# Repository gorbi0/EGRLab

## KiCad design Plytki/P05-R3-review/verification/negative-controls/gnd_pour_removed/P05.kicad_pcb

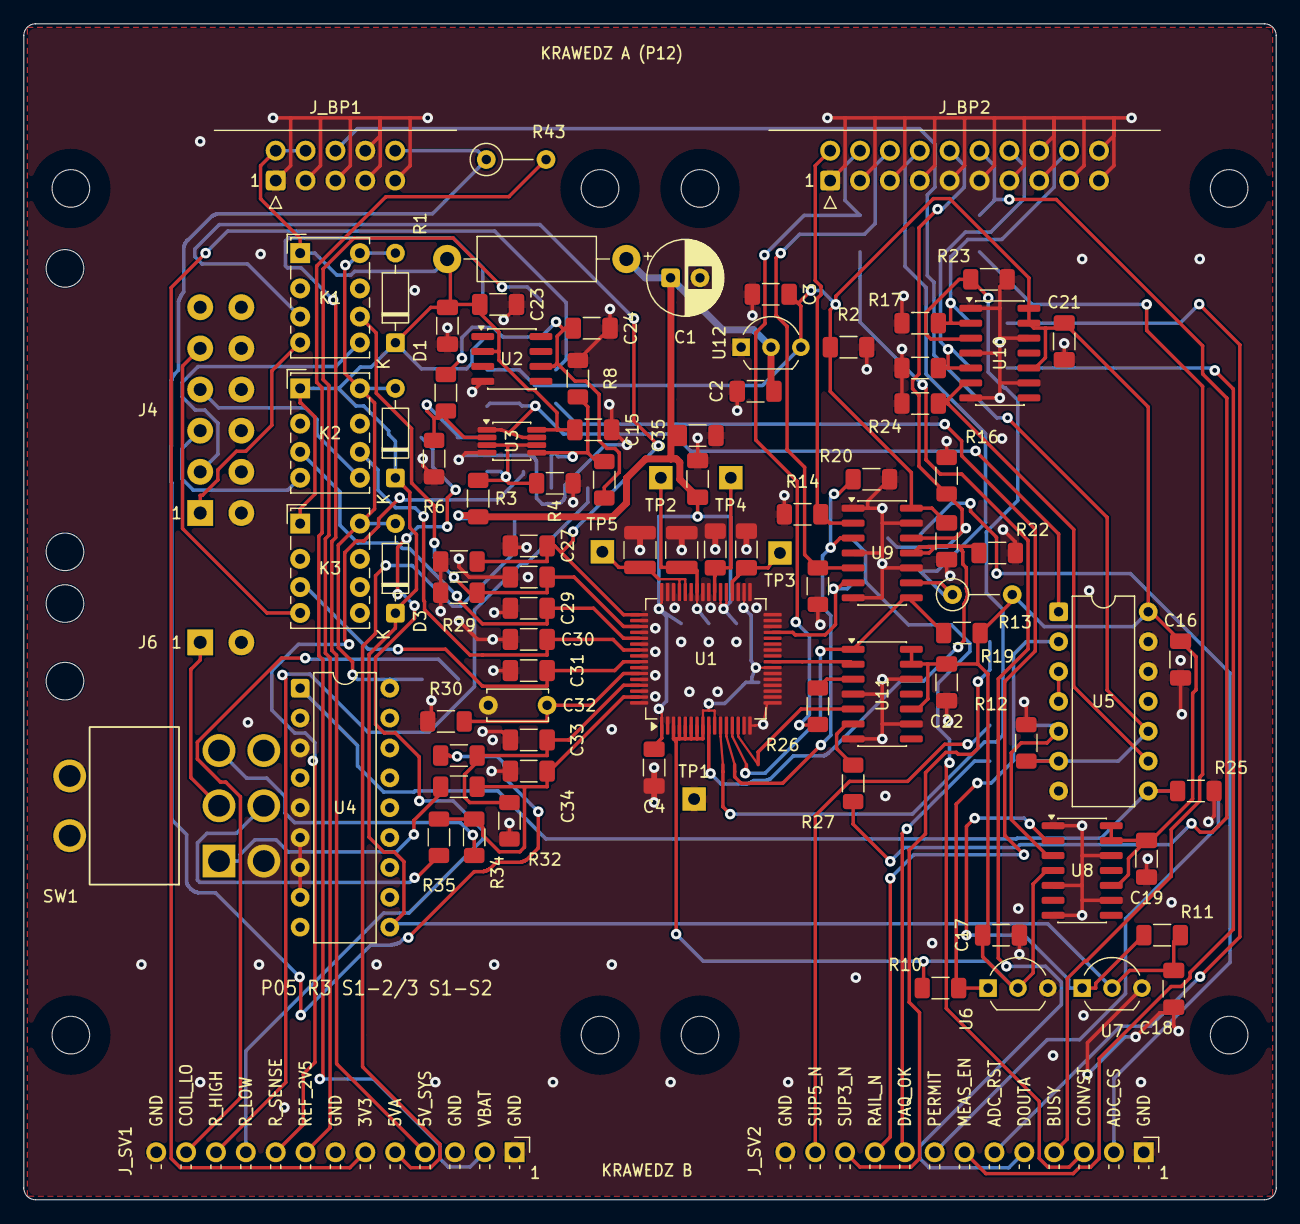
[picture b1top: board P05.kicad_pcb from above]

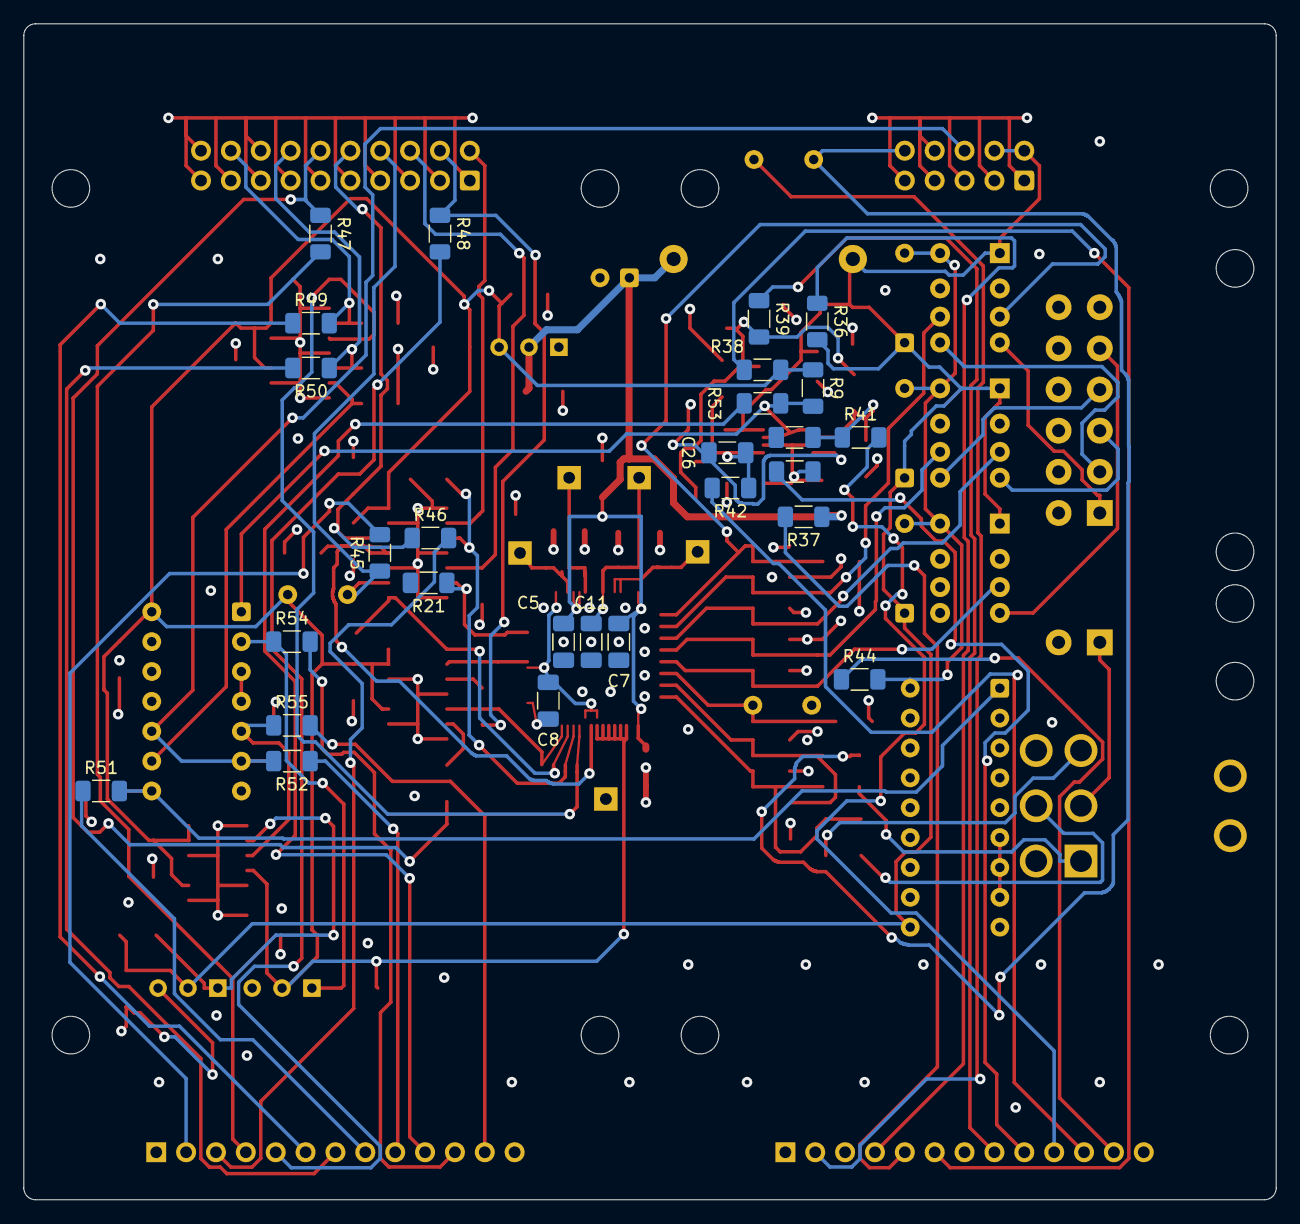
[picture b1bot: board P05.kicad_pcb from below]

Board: 2 copper layers, 106.5 x 100.0 mm, 128 parts (27 on the bottom side), 76 nets.

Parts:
C1: 220u / 16V; CP_Radial_D6.3mm_P2.50mm
C2, C9, C10, C23, C24: 1u; C_1206_3216Metric_Pad1.33x1.80mm_HandSolder
C3: 2.2u; C_1206_3216Metric_Pad1.33x1.80mm_HandSolder
C4, C5, C6, C7, C8, C11, C14, C15, C16, C17, C18, C19, C20, C21, C22: 100n; C_1206_3216Metric_Pad1.33x1.80mm_HandSolder
C12, C13: 22u; C_1210_3225Metric
C25, C26: 10n; C_1206_3216Metric_Pad1.33x1.80mm_HandSolder
C27, C28, C29, C30, C31, C33, C34: 220p; C_1206_3216Metric_Pad1.33x1.80mm_HandSolder
C32: 1n; C_Disc_D5.0mm_W2.5mm_P5.00mm
C35: 10u; C_1206_3216Metric_Pad1.33x1.80mm_HandSolder
D1, D2, D3: 1N4148; D_DO-35_SOD27_P7.62mm_Horizontal
H1, H2, H3, H4, H5, H6, H7, H8: M3 NPTH
J4: TAPS / PTH; PTH_TAPS_12
J6: AUX / coax 50mm; PTH_AUX_2
J_BP1: J_BP1 / IDC 2x5; IDC-Header_2x05_P2.54mm_Horizontal
J_BP2: J_BP2 / IDC 2x10; IDC-Header_2x10_P2.54mm_Horizontal
J_SV1: J_SV1 SERWIS 1x13; PinHeader_1x13_P2.54mm_Horizontal
J_SV2: J_SV2 SERWIS 1x13; PinHeader_1x13_P2.54mm_Horizontal
K1, K2, K3: G6K-2P-Y DC5; Relay_DPDT_Omron_G6K-2P-Y
R1: 1R; R_Axial_DIN0411_L9.9mm_D3.6mm_P15.24mm_Horizontal
R2, R36, R37, R38, R44, R45, R46, R47, R48, R49, R50, R51, R52, R55: 1K; R_1206_3216Metric_Pad1.30x1.75mm_HandSolder
R3: 15K; R_1206_3216Metric_Pad1.30x1.75mm_HandSolder
R4, R9, R10, R11, R12, R14, R15, R16, R17, R18, R19, R20, R21, R22, R23, R24, R25, R30, R39, R40, R41, R42, R53, R54: 10K; R_1206_3216Metric_Pad1.30x1.75mm_HandSolder
R5: 6.04K; R_1206_3216Metric_Pad1.30x1.75mm_HandSolder
R6: 20K; R_1206_3216Metric_Pad1.30x1.75mm_HandSolder
R7: 5.11K; R_1206_3216Metric_Pad1.30x1.75mm_HandSolder
R8: 24.9K; R_1206_3216Metric_Pad1.30x1.75mm_HandSolder
R13: 47K; R_Axial_DIN0207_L6.3mm_D2.5mm_P5.08mm_Vertical
R26, R27: 33R; R_1206_3216Metric_Pad1.30x1.75mm_HandSolder
R28, R29, R32, R34, R35: 100K; R_1206_3216Metric_Pad1.30x1.75mm_HandSolder
R31: 499K; R_1206_3216Metric_Pad1.30x1.75mm_HandSolder
R33: 300K; R_1206_3216Metric_Pad1.30x1.75mm_HandSolder
R43: 4.7K; R_Axial_DIN0207_L6.3mm_D2.5mm_P5.08mm_Vertical
SW1: AUX HI / LO; ESW_100DP_M6
TP1: GND; TestPad_1
TP2: ADC_REF; TestPad_1
TP3: REGCAP_A; TestPad_1
TP4: REGCAP_D; TestPad_1
TP5: REFCAP; TestPad_1
U1: AD7606BBSTZ; LQFP-64_10x10mm_P0.5mm
U2: REF5025IDR; SOIC-8_3.9x4.9mm_P1.27mm
U3: TLV1702-Q1; VSSOP-8_3x3mm_P0.65mm
U4: TBD62083APG; DIP-18_W7.62mm
U5: SN74HC08N; DIP-14_W7.62mm
U6: MCP120-300DI/TO; TO-92_Inline_Wide
U7: MCP120-450DI/TO; TO-92_Inline_Wide
U8, U9, U10, U11: 74LVC125AD; SOIC-14_3.9x8.7mm_P1.27mm
U12: MCP1700-3302E/TO; TO-92_Inline_Wide

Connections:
3V3_DAQ: C3.1, C8.1, C16.1, C17.1, C19.1, C20.1, C21.1, C22.1, R2.1, R9.2, R10.2, R13.2, R19.2, R38.1, U1.3, U1.4, U1.5, U1.6, U1.7, U1.8, U1.10, U1.23, U1.34, U5.14, U6.2, U8.4, U8.10, U8.13, U8.14, U9.14, U10.10, U10.13, U10.14, U11.10, U11.13, U11.14, U12.3
5VA_P05: C1.1, C2.1, C4.1, C5.1, C6.1, C7.1, C35.1, R1.2, R3.1, R37.1, U1.1, U1.37, U1.38, U1.48, U12.2
5V_SYS: C14.1, C15.1, C18.1, C23.1, D1.1, D2.1, D3.1, J_BP1.2, J_BP1.4, K1.1, K2.1, K3.1, R1.1, R11.2, R36.1, U2.2, U3.8, U4.10, U7.2
/AUX_IN/AUX_HI: R33.1, SW1.1
/AUX_IN/AUX_IN: J6.1, SW1.2
/AUX_IN/AUX_LO: R34.1, SW1.3
/AUX_IN/AUX_SHUNT: R35.2, SW1.5
/DIG/BUSY_SER: R27.1, U11.6
/DIG/DOUT_SER: R26.1, U11.3
/READY/DAQ_TWO_OK: U5.3, U5.4
/READY/P05_SUP5_RAW: R11.1, U7.1, U8.2
/SERWIS/SRV_3V3_DAQ: J_SV1.6, R38.2
/SERWIS/SRV_5VA_P05: J_SV1.5, R37.2
/SERWIS/SRV_5V_SYS: J_SV1.4, R36.2
/SERWIS/SRV_ADC_BUSY: J_SV2.4, R47.2
/SERWIS/SRV_ADC_CONVST: J_SV2.3, R46.2
/SERWIS/SRV_ADC_CS: J_SV2.2, R45.2
/SERWIS/SRV_ADC_DOUTA: J_SV2.5, R48.2
/SERWIS/SRV_ADC_RESET: J_SV2.6, R49.2
/SERWIS/SRV_DAQ_OK: J_SV2.9, R52.2
/SERWIS/SRV_DAQ_RAIL_N: J_SV2.10, R53.2
/SERWIS/SRV_MEAS_COIL_LOW: J_SV1.12, R44.2
/SERWIS/SRV_MEAS_EN: J_SV2.7, R50.2
/SERWIS/SRV_MEAS_PERMIT: J_SV2.8, R51.2
/SERWIS/SRV_P05_SUP3_N: J_SV2.11, R54.2
/SERWIS/SRV_P05_SUP5_N: J_SV2.12, R55.2
/SERWIS/SRV_RAIL_HIGH: J_SV1.11, R42.2
/SERWIS/SRV_RAIL_LOW: J_SV1.10, R41.2
/SERWIS/SRV_RAIL_SENSE: J_SV1.9, R40.2
/SERWIS/SRV_REF_2V5: J_SV1.8, R39.2
/SERWIS/SRV_VBAT_SENSE: J_SV1.2, R43.2
ADC_BUSY: J_BP2.12, R27.2, R47.1
ADC_CH1: C27.1, K1.3, R28.1, U1.49
ADC_CH2: C28.1, K1.6, R29.1, U1.51
ADC_CH3: C29.1, K2.3, U1.53
ADC_CH4: C30.1, K2.6, U1.55
ADC_CH5: C31.1, K3.3, U1.57
ADC_CH6: C32.1, R30.1, U1.59
ADC_CH7: C33.1, R31.2, R32.1, U1.61
ADC_CH8: C34.1, R33.2, R34.2, R35.1, U1.63
ADC_CONVST: J_BP2.10, R16.1, R46.1, U9.12
ADC_CONVST_P05: R22.1, U1.9, U9.11
ADC_CS: J_BP2.8, R13.1, R45.1, U9.9
ADC_CS_P05: R19.1, U1.13, U9.8, U11.1
ADC_DOUTA: J_BP2.4, R26.2, R48.1
ADC_REF: C11.1, C12.1, TP2.1, U1.42
ADC_RESET: J_BP2.18, R17.1, R49.1, U10.2
ADC_RESET_P05: R23.1, U1.11, U10.3
ADC_SCLK: J_BP2.2, R14.1, U9.2
ADC_SCLK_P05: R20.1, U1.12, U9.3
ADC_SDI: J_BP2.6, R15.1, U9.5
ADC_SDI_P05: R21.1, U1.29, U9.6
AD_BUSY_LOCAL: U1.14, U11.5
AD_DOUT_LOCAL: U1.24, U11.2
DAQ_OK: J_BP1.6, R12.1, R52.1, U5.6, U5.10
DAQ_RAIL_N: R9.1, R53.1, U3.1, U3.7, U5.1
GND: C1.2, C2.2, C3.2, C4.2, C5.2, C6.2, C7.2, C8.2, C9.2, C10.2, C11.2, C12.2, C13.2, C14.2, C15.2, C16.2, C17.2, C18.2, C19.2, C20.2, C21.2, C22.2, C23.2, C24.2, C25.2, C26.2, C27.2, C28.2, C29.2, C30.2, C31.2, C32.2, C33.2, C34.2, C35.2, J4.2, J4.4, J4.6, J4.8, J4.10, J6.2, J_BP1.1, J_BP1.3, J_BP1.5, J_BP1.7, J_BP1.8, J_BP1.9, J_BP2.1, J_BP2.3, J_BP2.5, J_BP2.7, J_BP2.9, J_BP2.11, J_BP2.13, J_BP2.15, J_BP2.16, J_BP2.17, J_BP2.19, J_BP2.20, J_SV1.1, J_SV1.3, J_SV1.7, J_SV1.13, J_SV2.1, J_SV2.13, R2.2, R4.2, R6.2, R8.2, R12.2, R14.2, R15.2, R16.2, R17.2, R18.2, R20.2, R21.2, R22.2, R23.2, R24.2, R25.2, R28.2, R29.2, R30.2, R32.2, SW1.4, TP1.1, U1.2, U1.16, U1.17, U1.18, U1.19, U1.20, U1.21, U1.22, U1.26, U1.30, U1.31, U1.32, U1.33, U1.35, U1.40, U1.41, U1.43, U1.46, U1.47, U1.50, U1.52, U1.54, U1.56, U1.58, U1.60, U1.62, U1.64, U2.4, U3.4, U4.2, U4.3, U4.4, U4.5, U4.6, U4.7, U4.8, U4.9, U5.7, U5.12, U5.13, U6.3, U7.3, U8.1, U8.5, U8.7, U8.9, U8.12, U9.1, U9.4, U9.7, U9.10, U9.13, U10.1, U10.4, U10.7, U10.9, U10.12, U11.4, U11.7, U11.9, U11.12, U12.1
MEAS_COIL_LOW: D1.2, D2.2, D3.2, K1.8, K2.8, K3.8, R44.1, U4.18
MEAS_EN: J_BP2.14, R18.1, R50.1, U10.5
MEAS_EN_P05: R24.1, U5.9, U10.6
MEAS_PERMIT: R25.1, R51.1, U4.1, U5.8
P05_SUP3_N: R10.1, R54.1, U5.2, U6.1
P05_SUP5_N: R55.1, U5.5, U8.3
RAIL_HIGH: C26.1, R7.2, R8.1, R42.1, U3.5
RAIL_LOW: C25.1, R5.2, R6.1, R41.1, U3.2
RAIL_SENSE: R3.2, R4.1, R40.1, U3.3, U3.6
REFCAP: C13.1, TP5.1, U1.44, U1.45
REF_2V5: C24.1, R5.1, R7.1, R39.1, U2.6
REGCAP_A: C9.1, TP3.1, U1.36
REGCAP_D: C10.1, TP4.1, U1.39
TAP_P1: J4.1, K1.4
TAP_P3: J4.3, K1.5
TAP_P4: J4.5, K2.4
TAP_P5: J4.7, K2.5
TAP_P6: J4.9, K3.4
VBAT_SENSE: J_BP1.10, R31.1, R43.1
